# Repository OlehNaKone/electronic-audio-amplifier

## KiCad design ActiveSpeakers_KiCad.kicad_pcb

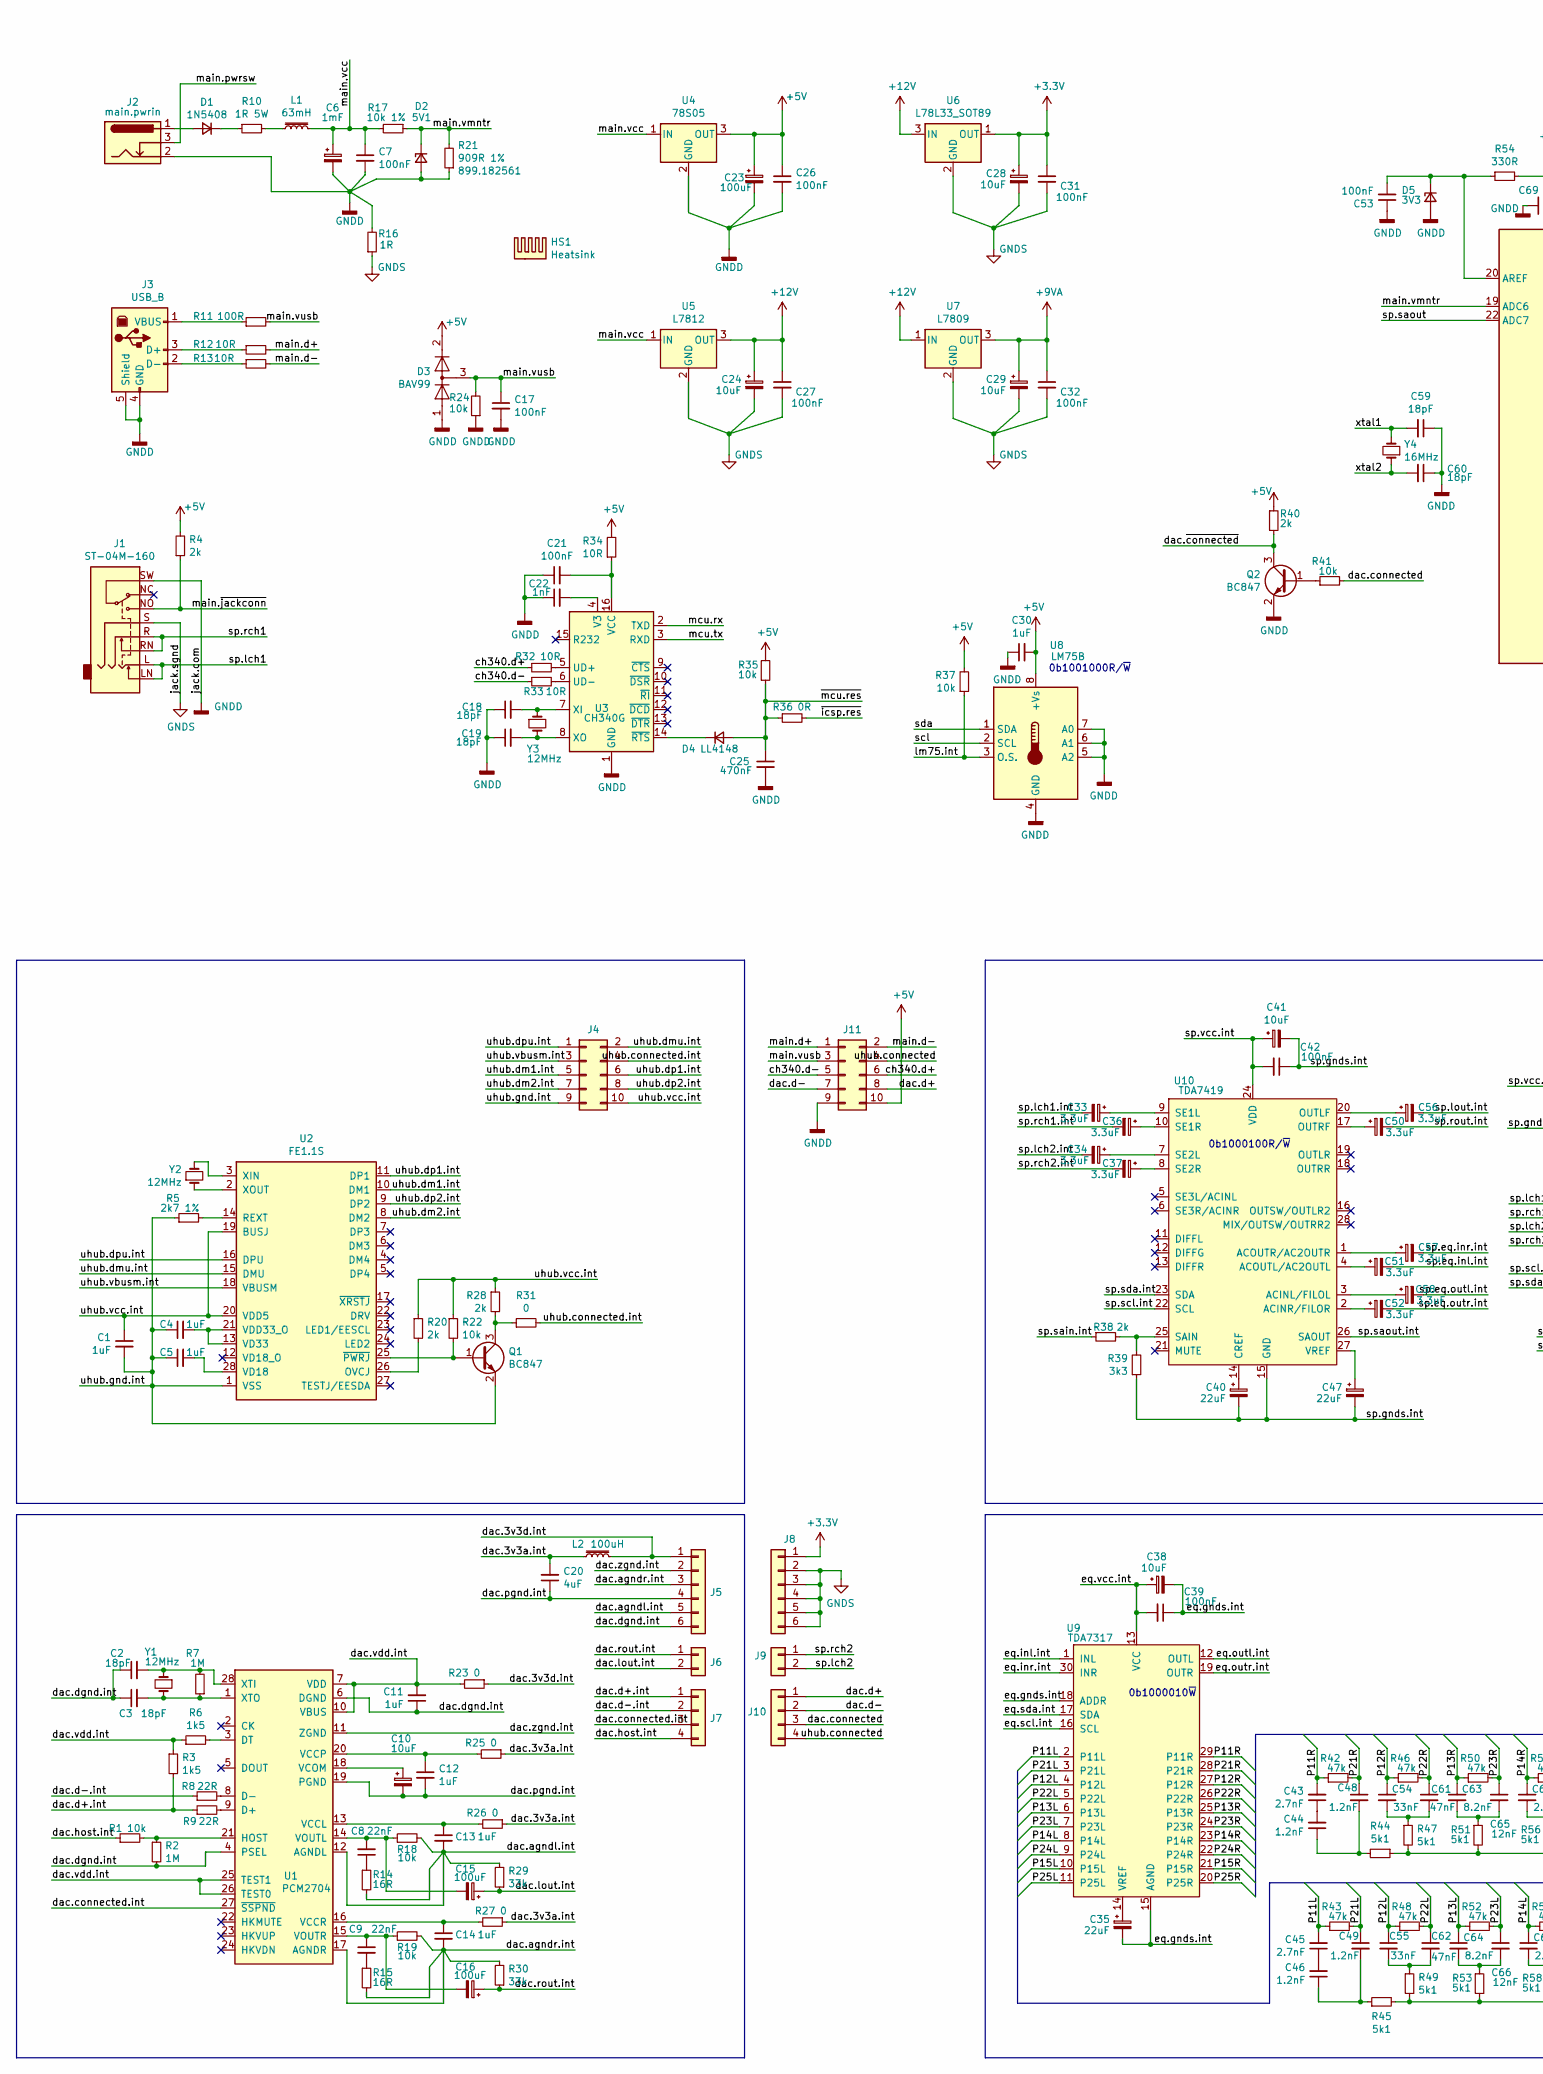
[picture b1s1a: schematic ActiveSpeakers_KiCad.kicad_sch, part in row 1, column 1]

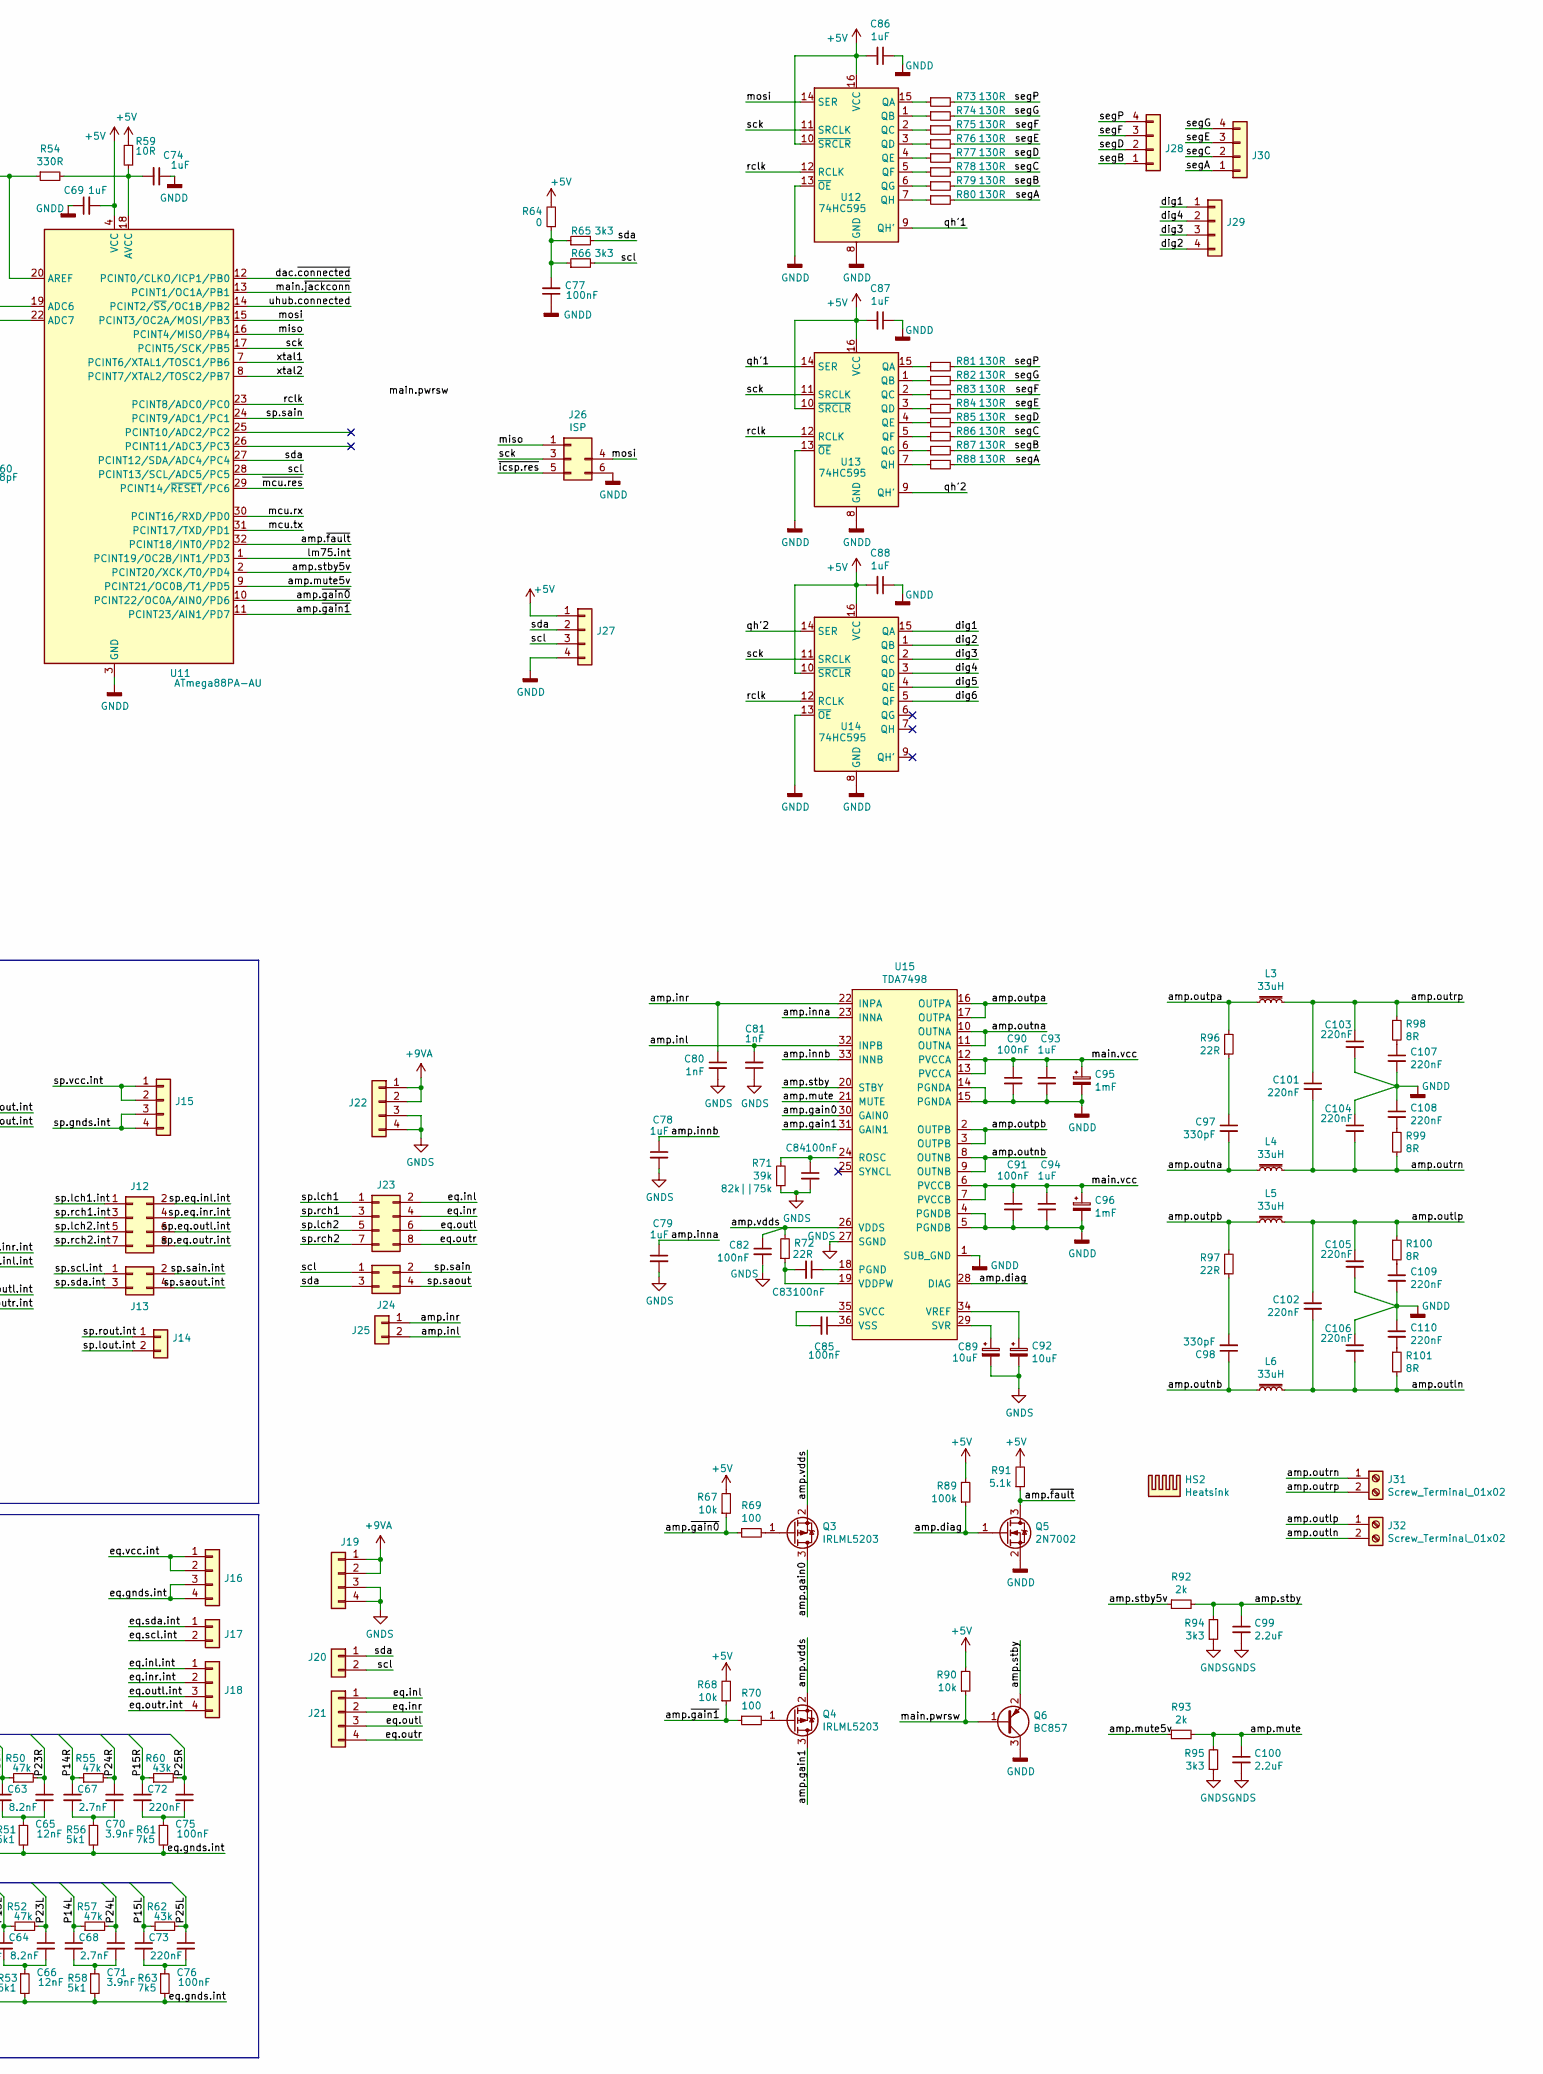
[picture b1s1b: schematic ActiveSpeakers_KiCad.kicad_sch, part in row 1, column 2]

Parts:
C1, C11, C12, C13, C14, C30, C69, C74, C86, C87, C88, C93, C94: 1uF; C_1206_3216Metric_Pad1.42x1.75mm_HandSolder
C2, C3, C18, C19, C59, C60: 18pF; C_0805_2012Metric_Pad1.15x1.40mm_HandSolder
C4, C5: 1uF; C_0805_2012Metric_Pad1.15x1.40mm_HandSolder
C6, C95, C96: 1mF; CP_Radial_D12.5mm_P5.00mm
C7, C39, C42, C75, C76: 100nF; C_Rect_L7.2mm_W2.5mm_P5.00mm_FKS2_FKP2_MKS2_MKP2
C8, C9: 22nF; C_Rect_Flat_L7.2mm_W2.5mm_P5.00mm_FKS2_FKP2_MKS2_MKP2
C10: 10uF; CP_Radial_D4.0mm_P2.00mm
C15, C16, C23: 100uF; CP_Radial_D6.3mm_P2.50mm
C17, C21, C26, C27, C31, C32, C53, C77, C83, C90, C91: 100nF; C_1206_3216Metric_Pad1.42x1.75mm_HandSolder
C20: 4uF; C_1206_3216Metric_Pad1.42x1.75mm_HandSolder
C22: 1nF; C_0805_2012Metric_Pad1.15x1.40mm_HandSolder
C24, C28, C29, C38, C41: 10uF; CP_Radial_D5.0mm_P2.54mm
C25: 470nF; C_1206_3216Metric_Pad1.42x1.75mm_HandSolder
C33, C34, C36, C37, C50, C51, C52, C56, C57, C58: 3.3uF; CP_Radial_D5.0mm_P2.54mm
C35, C40, C47: 22uF; CP_Radial_D5.0mm_P2.54mm
C43, C45: 2.7nF; C_Rect_L7.0mm_W3.5mm_P5.00mm
C44, C46, C48, C49: 1.2nF; C_Rect_L7.2mm_W2.5mm_P5.00mm_FKS2_FKP2_MKS2_MKP2
C54, C55: 33nF; C_Rect_L7.2mm_W2.5mm_P5.00mm_FKS2_FKP2_MKS2_MKP2
C61, C62: 47nF; C_Rect_L7.2mm_W2.5mm_P5.00mm_FKS2_FKP2_MKS2_MKP2
C63, C64: 8.2nF; C_Rect_L7.0mm_W3.5mm_P5.00mm
C65, C66: 12nF; C_Rect_L7.0mm_W3.5mm_P5.00mm
C67, C68: 2.7nF; C_Rect_L7.2mm_W2.5mm_P5.00mm_FKS2_FKP2_MKS2_MKP2
C70, C71: 3.9nF; C_Rect_L7.0mm_W3.5mm_P5.00mm
C72, C73, C103, C104, C105, C106, C107, C108, C109, C110: 220nF; C_Rect_L7.2mm_W2.5mm_P5.00mm_FKS2_FKP2_MKS2_MKP2
C78: 1uF; CP_Radial_Flat_Mirrored_D4.0mm_P2.00mm
C79: 1uF; CP_Radial_Flat_D4.0mm_P2.00mm
C80, C81: 1nF; C_Rect_Flat_L7.2mm_W2.5mm_P5.00mm_FKS2_FKP2_MKS2_MKP2
C82, C85: 100nF; C_0603_1608Metric_Pad1.05x0.95mm_HandSolder
C84: 100nF; C_0805_2012Metric_Pad1.15x1.40mm_HandSolder
C89, C92: 10uF; CP_Radial_Flat_Mirrored_D4.0mm_P2.00mm
C97, C98: 330pF; C_Rect_Flat_L7.2mm_W2.5mm_P5.00mm_FKS2_FKP2_MKS2_MKP2
C99, C100: 2.2uF; C_0805_2012Metric_Pad1.15x1.40mm_HandSolder
C101, C102: 220nF; C_Rect_L7.0mm_W3.5mm_P5.00mm
D1: 1N5408; D_DO-201AD_P12.70mm_Horizontal
D2: 5V1; D_MiniMELF
D3: BAV99; SOT-23
D4: LL4148; D_MiniMELF
D5: 3V3; D_MiniMELF
HS1: Heatsink; Heatsink_Fischer_SK104-STC-STIC_35x13mm_2xDrill2.5mm
HS2: Heatsink; Heatsink_50.2x72.1mm_4xFixation3mm
J1: ST-04M-160; Jack_3.5mm_CUI_SJ-3568N_Horizontal
J2: main.pwrin; BarrelJack_Horizontal
J3: USB_B; USB_B_OST_USB-B1HSxx_Horizontal
J4: Conn_02x05; PinHeader_2x05_P2.54mm_Horizontal
J5: Conn_01x06; PinHeader_1x06_P2.54mm_Horizontal
J6, J14, J17: Conn_01x04; PinHeader_1x02_P2.54mm_Horizontal
J7, J15, J16, J18: Conn_01x04; PinHeader_1x04_P2.54mm_Horizontal
J8: Conn_01x06; PinSocket_1x06_P2.54mm_Vertical
J9, J20, J25: Conn_01x04; PinSocket_1x02_P2.54mm_Vertical
J10, J19, J21, J22: Conn_01x04; PinSocket_1x04_P2.54mm_Vertical
J11: Conn_02x05; PinSocket_2x05_P2.54mm_Vertical
J12: Conn_02x04; PinHeader_2x04_P2.54mm_Horizontal
J13: Conn_01x04; PinHeader_2x02_P2.54mm_Horizontal
J23: Conn_01x04; PinSocket_2x04_P2.54mm_Vertical
J24: Conn_01x04; PinSocket_2x02_P2.54mm_Vertical
J26: ISP; AVR_ICSP_Without_VCC_P2.54mm
J27, J28, J29, J30: Conn_01x04; SolderWirePad_1x04_P3.175mm_Drill0.8mm
J31, J32: Screw_Terminal_01x02; TerminalBlock_bornier-2_P5.08mm
L1: 63mH; L_Toroid_Vertical_L17.8mm_W8.1mm_P7.62mm_Bourns_5700
L2: 100uH; L_1210_3225Metric_Pad1.42x2.65mm_HandSolder
L3, L4, L5, L6: 33uH; L_12x12mm_H8mm
Q1, Q2: BC847; SOT-23
Q3, Q4: IRLML5203; SOT-23
Q5: 2N7002; SOT-23
Q6: BC857; SOT-23
R1, R18, R19, R22, R37, R41, R67, R68, R90: 10k; R_0805_2012Metric_Pad1.15x1.40mm_HandSolder
R2, R7: 1M; R_1206_3216Metric_Pad1.42x1.75mm_HandSolder
R3, R6: 1k5; R_0603_1608Metric_Pad1.05x0.95mm_HandSolder
R4, R20, R28, R92, R93: 2k; R_0805_2012Metric_Pad1.15x1.40mm_HandSolder
R5: 2k7 1%; R_0805_2012Metric_Pad1.15x1.40mm_HandSolder
R8, R9: 22R; R_1206_3216Metric_Pad1.42x1.75mm_HandSolder
R10: 1R 5W; R_Axial_Power_L25.0mm_W9.0mm_P7.62mm_Vertical
R11: 100R; R_1206_3216Metric_Pad1.42x1.75mm_HandSolder
R12, R13, R32, R33, R34, R59: 10R; R_1206_3216Metric_Pad1.42x1.75mm_HandSolder
R14, R15: 16R; R_1206_3216Metric_Pad1.42x1.75mm_HandSolder
R16: 1R; R_2512_6332Metric_Pad1.52x3.35mm_HandSolder
R17: 10k 1%; R_0805_2012Metric_Pad1.15x1.40mm_HandSolder
R21: 909R 1%; R_0603_1608Metric_Pad1.05x0.95mm_HandSolder
R23, R25, R26, R27, R31, R64: 0; R_1206_3216Metric_Pad1.42x1.75mm_HandSolder
R24, R35: 10k; R_1206_3216Metric_Pad1.42x1.75mm_HandSolder
R29, R30: 33k; R_0805_2012Metric_Pad1.15x1.40mm_HandSolder
R36: 0R; R_1206_3216Metric_Pad1.42x1.75mm_HandSolder
R38, R40: 2k; R_1206_3216Metric_Pad1.42x1.75mm_HandSolder
R39: 3k3; R_1206_3216Metric_Pad1.42x1.75mm_HandSolder
R42, R43, R46, R48, R50, R52, R55, R57: 47k; R_0805_2012Metric_Pad1.15x1.40mm_HandSolder
R44, R45, R47, R49, R51, R53, R56, R58: 5k1; R_0805_2012Metric_Pad1.15x1.40mm_HandSolder
R54: 330R; R_1206_3216Metric_Pad1.42x1.75mm_HandSolder
R60, R62: 43k; R_0805_2012Metric_Pad1.15x1.40mm_HandSolder
R61, R63: 7k5; R_0805_2012Metric_Pad1.15x1.40mm_HandSolder
R65, R66, R94, R95: 3k3; R_0805_2012Metric_Pad1.15x1.40mm_HandSolder
R69, R70: 100; R_0805_2012Metric_Pad1.15x1.40mm_HandSolder
R71: 39k; R_0805_2012Metric_Pad1.15x1.40mm_HandSolder
R72: 22R; R_0805_2012Metric_Pad1.15x1.40mm_HandSolder
R73, R74, R75, R76, R77, R78, R79, R80, R81, R82, R83, R84, R85, R86, R87, R88: 130R; R_0805_2012Metric_Pad1.15x1.40mm_HandSolder
R89: 100k; R_0805_2012Metric_Pad1.15x1.40mm_HandSolder
R91: 5.1k; R_0805_2012Metric_Pad1.15x1.40mm_HandSolder
R96, R97: 22R; R_Axial_DIN0207_L6.3mm_D2.5mm_P10.16mm_Horizontal
R98, R99, R100, R101: 8R; R_2512_6332Metric_Pad1.52x3.35mm_HandSolder
U1: PCM2704; SSOP-28_5.3x10.2mm_P0.65mm
U2: FE1.1S; SSOP-28_3.9x9.9mm_P0.635mm
U3: CH340G; SOIC-16_3.9x9.9mm_P1.27mm
U4: 78S05; TO-220-3_Vertical
U5: L7812; TO-252-2
U6: L78L33_SOT89; SOT-89-3
U7: L7809; TO-252-2
U8: LM75B; SOIC-8_3.9x4.9mm_P1.27mm
U9: TDA7317; SDIP-30_W10.16mm
U10: TDA7419; SOIC-28W_7.5x17.9mm_P1.27mm
U11: ATmega88PA-AU; TQFP-32_7x7mm_P0.8mm
U12, U13, U14: 74HC595; SOIC-16_3.9x9.9mm_P1.27mm
U15: TDA7498; ST_PowerSSO-36_EPU_SlugUp
Y1: 12MHz; Crystal_SMD_HC49-SD
Y2: 12MHz; Crystal_DS26_D2.0mm_L6.0mm_Horizontal
Y3: 12MHz; Crystal_DS26_D2.0mm_L6.0mm_Horizontal_1EP_style2
Y4: 16MHz; Crystal_SMD_HC49-SD

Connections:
+3V3: C28.1, C31.1, J8.1, U6.1 (OUT)
+5V: C23.1, C26.1, C30.2, C69.2, C86.2, C87.2, C88.2, D3.2 (A), J11.10, J27.1, R4.2, R34.2, R35.2, R37.2, R40.1, R59.1, R64.2, R67.2, R68.2, R89.2, R90.2, R91.2, U4.3 (OUT), U8.8 (+Vs), U11.4 (VCC), U11.6 (VCC), U12.10 (~SRCLR), U12.16 (VCC), U13.10 (~SRCLR), U13.16 (VCC), U14.10 (~SRCLR), U14.16 (VCC)
+9VA: C29.1, C32.1, J19.1, J19.2, J22.1, J22.2, U7.3 (OUT)
+12V: C24.1, C27.1, U5.3 (OUT), U6.3 (IN), U7.1 (IN)
/P11L: C45.2, R43.1, U9.2 (P11L)
/P11R: C43.2, R42.1, U9.29 (P11R)
/P12L: C55.1, R48.1, U9.4 (P12L)
/P12R: C54.1, R46.1, U9.27 (P12R)
/P13L: C64.1, R52.1, U9.6 (P13L)
/P13R: C63.1, R50.1, U9.25 (P13R)
/P14L: C68.1, R57.1, U9.8 (P14L)
/P14R: C67.1, R55.1, U9.23 (P14R)
/P15L: C73.1, R62.1, U9.10 (P15L)
/P15R: C72.1, R60.1, U9.21 (P15R)
/P21L: C49.1, R43.2, U9.3 (P21L)
/P21R: C48.1, R42.2, U9.28 (P21R)
/P22L: C62.1, R48.2, U9.5 (P22L)
/P22R: C61.1, R46.2, U9.26 (P22R)
/P23L: C66.1, R52.2, U9.7 (P23L)
/P23R: C65.1, R50.2, U9.24 (P23R)
/P24L: C71.1, R57.2, U9.9 (P24L)
/P24R: C70.1, R55.2, U9.22 (P24R)
/P25L: C76.1, R62.2, U9.11 (P25L)
/P25R: C75.1, R60.2, U9.20 (P25R)
/amp.diag: Q5.1 (G), R89.1, U15.28 (DIAG)
/amp.gain0: Q3.3 (D), U15.30 (GAIN0)
/amp.gain1: Q4.3 (D), U15.31 (GAIN1)
/amp.inl: C81.2, J25.2, U15.32 (INPB)
/amp.inna: C79.1, U15.23 (INNA)
/amp.innb: C78.1, U15.33 (INNB)
/amp.inr: C80.1, J25.1, U15.22 (INPA)
/amp.mute: C100.1, R93.2, R95.2, U15.21 (MUTE)
/amp.mute5v: R93.1, U11.9 (PCINT21/OC0B/T1/PD5)
/amp.outln: C102.2, C106.2, J32.2, L6.2, R101.2
/amp.outlp: C102.1, C105.1, J32.1, L5.2, R100.1
/amp.outna: C97.2, L4.1, U15.10 (OUTNA), U15.11 (OUTNA)
/amp.outnb: C98.1, L6.1, U15.8 (OUTNB), U15.9 (OUTNB)
/amp.outpa: L3.1, R96.2, U15.16 (OUTPA), U15.17 (OUTPA)
/amp.outpb: L5.1, R97.2, U15.2 (OUTPB), U15.3 (OUTPB)
/amp.outrn: C101.2, C104.2, J31.1, L4.2, R99.2
/amp.outrp: C101.1, C103.1, J31.2, L3.2, R98.1
/amp.stby: C99.1, Q6.2 (E), R92.2, R94.2, U15.20 (STBY)
/amp.stby5v: R92.1, U11.2 (PCINT20/XCK/T0/PD4)
/amp.vdds: C82.1, Q3.2 (S), Q4.2 (S), R72.2, U15.26 (VDDS)
/amp.~fault: Q5.3 (D), R91.1, U11.32 (PCINT18/INT0/PD2)
/amp.~gain0: R67.1, R69.1, U11.10 (PCINT22/OC0A/AIN0/PD6)
/amp.~gain1: R68.1, R70.1, U11.11 (PCINT23/AIN1/PD7)
/ch340.d+: J11.6, R32.1
/ch340.d-: J11.5, R33.1
/dac.3v3a.int: C20.2, L2.1, R25.1, R26.1, R27.1
/dac.3v3d.int: J5.1, L2.2, R23.1
/dac.agndl.int: C13.2, J5.5, R14.2, R18.2, R29.2, U1.12 (AGNDL)
/dac.agndr.int: C14.2, J5.3, R15.2, R19.2, R30.2, U1.17 (AGNDR)
/dac.connected: J10.3, R41.2
/dac.connected.int: J7.3, U1.27 (~SSPND)
/dac.d+: J10.1, J11.8
/dac.d+.int: J7.1, R3.2, R9.1
/dac.d-: J10.2, J11.7
/dac.d-.int: J7.2, R8.1
/dac.dgnd.int: C2.1, C3.1, C11.1, J5.6, R2.2, U1.4 (PSEL), U1.6 (DGND)
/dac.host.int: J7.4, R1.1
/dac.lout.int: C15.1, J6.2, R29.1
/dac.pgnd.int: C10.2, C12.2, C20.1, J5.4, U1.19 (PGND)
/dac.rout.int: C16.1, J6.1, R30.1
/dac.vdd.int: C11.2, R3.1, R6.1, R23.2, U1.7 (VDD), U1.10 (VBUS), U1.25 (TEST1), U1.26 (TEST0)
/dac.zgnd.int: J5.2, U1.11 (ZGND)
/dac.~connected: Q2.3 (C), R40.2, U11.12 (PCINT0/CLKO/ICP1/PB0)
/dig1: J29.1, U14.15 (QA)
/dig2: J29.4, U14.1 (QB)
/dig3: J29.3, U14.2 (QC)
/dig4: J29.2, U14.3 (QD)
/eq.gnds.int: C35.2, C38.2, C39.1, J16.3, J16.4, R44.1, R45.2, R47.2, R49.2, R51.2, R53.2, R56.2, R58.2, R61.2, R63.2, U9.15 (AGND), U9.18 (ADDR)
/eq.inl: J21.1, J23.2
/eq.inl.int: J18.1, U9.1 (INL)
/eq.inr: J21.2, J23.4
/eq.inr.int: J18.2, U9.30 (INR)
/eq.outl: J21.3, J23.6
/eq.outl.int: J18.3, U9.12 (OUTL)
/eq.outr: J21.4, J23.8
/eq.outr.int: J18.4, U9.19 (OUTR)
/eq.scl.int: J17.2, U9.16 (SCL)
/eq.sda.int: J17.1, U9.17 (SDA)
/eq.vcc.int: C38.1, C39.2, J16.1, J16.2, U9.13 (VCC)
/lm75.int: R37.1, U8.3 (O.S.), U11.1 (PCINT19/OC2B/INT1/PD3)
/main.d+: J11.1, R12.2
/main.d-: J11.2, R13.2
/main.pwrsw: J2.3, Q6.1 (B), R90.1
/main.vcc: C6.1, C7.1, C90.1, C91.1, C93.1, C94.1, C95.1, C96.1, L1.2, R17.2, U4.1 (IN), U5.1 (IN), U15.6 (PVCCB), U15.7 (PVCCB), U15.12 (PVCCA), U15.13 (PVCCA)
/main.vmntr: D2.1 (K), R17.1, R21.2, U11.19 (ADC6)
/main.vusb: C17.1, D3.3 (K), J11.3, R11.2, R24.2
/main.~jackconn: J1.NO, R4.1, U11.13 (PCINT1/OC1A/PB1)
/mcu.rx: U3.2 (TXD), U11.30 (PCINT16/RXD/PD0)
/mcu.tx: U3.3 (RXD), U11.31 (PCINT17/TXD/PD1)
/miso: J26.1 (MISO), U11.16 (PCINT4/MISO/PB4)
/mosi: J26.4 (MOSI), U11.15 (PCINT3/OC2A/MOSI/PB3), U12.14 (SER)
/qh'1: U12.9 (QH'), U13.14 (SER)
/qh'2: U13.9 (QH'), U14.14 (SER)
/rclk: U11.23 (PCINT8/ADC0/PC0), U12.12 (RCLK), U13.12 (RCLK), U14.12 (RCLK)
/sck: J26.3 (SCK), U11.17 (PCINT5/SCK/PB5), U12.11 (SRCLK), U13.11 (SRCLK), U14.11 (SRCLK)
/scl: J20.2, J24.1, J27.3, R66.2, U8.2 (SCL), U11.28 (PCINT13/SCL/ADC5/PC5)
/sda: J20.1, J24.3, J27.2, R65.2, U8.1 (SDA), U11.27 (PCINT12/SDA/ADC4/PC4)
/segA: J30.1, R80.2, R88.2
/segB: J28.1, R79.2, R87.2
/segC: J30.2, R78.2, R86.2
/segD: J28.2, R77.2, R85.2
/segE: J30.3, R76.2, R84.2
/segF: J28.3, R75.2, R83.2
/segG: J30.4, R74.2, R82.2
/segP: J28.4, R73.2, R81.2
/sp.eq.inl.int: C51.2, J12.2
/sp.eq.inr.int: C57.2, J12.4
/sp.eq.outl.int: C58.2, J12.6
/sp.eq.outr.int: C52.2, J12.8
/sp.gnds.int: C40.2, C41.2, C42.1, C47.2, J15.3, J15.4, R39.1, U10.15 (GND)
/sp.lch1: J1.L, J1.LN, J23.1
/sp.lch1.int: C33.2, J12.1
/sp.lch2: J9.2, J23.5
/sp.lch2.int: C34.2, J12.5
/sp.lout.int: C56.2, J14.2
/sp.rch1: J1.R, J1.RN, J23.3
/sp.rch1.int: C36.2, J12.3
/sp.rch2: J9.1, J23.7
/sp.rch2.int: C37.2, J12.7
/sp.rout.int: C50.2, J14.1
/sp.sain: J24.2, U11.24 (PCINT9/ADC1/PC1)
/sp.sain.int: J13.2, R38.1
/sp.saout: J24.4, U11.22 (ADC7)
/sp.saout.int: J13.4, U10.26 (SAOUT)
/sp.scl.int: J13.1, U10.22 (SCL)
/sp.sda.int: J13.3, U10.23 (SDA)
/sp.vcc.int: C41.1, C42.2, J15.1, J15.2, U10.24 (VDD)
/uhub.connected: J10.4, J11.4, U11.14 (PCINT2/~SS/OC1B/PB2)
/uhub.connected.int: J4.4, R31.2
/uhub.dm1.int: J4.5, U2.10 (DM1)
/uhub.dm2.int: J4.7, U2.8 (DM2)
/uhub.dmu.int: J4.2, U2.15 (DMU)
/uhub.dp1.int: J4.6, U2.11 (DP1)
/uhub.dp2.int: J4.8, U2.9 (DP2)
/uhub.dpu.int: J4.1, U2.16 (DPU)
/uhub.gnd.int: C1.2, C4.1, C5.1, J4.9, Q1.2 (E), R5.1, U2.1 (VSS)
/uhub.vbusm.int: J4.3, U2.18 (VBUSM)
/uhub.vcc.int: C1.1, J4.10, R20.1, R22.1, R28.1, U2.19 (BUSJ), U2.20 (VDD5)
/xtal1: C59.2, U11.7 (PCINT6/XTAL1/TOSC1/PB6), Y4.2
/xtal2: C60.2, U11.8 (PCINT7/XTAL2/TOSC2/PB7), Y4.1
/~icsp.res: J26.5 (~RESET), R36.2
/~mcu.res: C25.1, D4.2 (A), R35.1, R36.1, U11.29 (PCINT14/~RESET/PC6)
GNDD: C6.2, C7.2, C17.2, C18.1, C19.1, C21.1, C22.1, C23.2, C25.2, C26.2, C30.1, C53.1, C59.1, C60.1, C69.1, C74.1, C77.1, C86.1, C87.1, C88.1, C90.2, C91.2, C93.2, C94.2, C95.2, C96.2, C103.2, C104.1, C105.2, C106.1, C107.2, C108.1, C109.2, C110.1, D2.2 (A), D3.1 (K), D5.2 (A), J1.SW, J2.2, J3.4 (GND), J3.5 (Shield), J11.9, J26.6 (GNDD), J27.4, Q2.2 (E), Q5.2 (S), Q6.3 (C), R16.2, R21.1, R24.1, U3.1 (GND), U4.2 (GND), U8.4 (GND), U8.5 (A2), U8.6 (A1), U8.7 (A0), U11.3 (GND), U11.5 (GND), U11.21 (GND), U12.8 (GND), U12.13 (~OE), U13.8 (GND), U13.13 (~OE), U14.8 (GND), U14.13 (~OE), U15.1 (SUB_GND), U15.4 (PGNDB), U15.5 (PGNDB), U15.14 (PGNDA), U15.15 (PGNDA)
GNDS: C24.2, C27.2, C28.2, C29.2, C31.2, C32.2, C78.2, C79.2, C80.2, C81.1, C82.2, C84.2, C89.2, C92.2, C99.2, C100.2, J1.S, J8.2, J8.3, J8.4, J8.5, J8.6, J19.3, J19.4, J22.3, J22.4, R16.1, R71.1, R94.1, R95.1, U5.2 (GND), U6.2 (GND), U7.2 (GND), U15.27 (SGND)
unnamed: C2.2, R7.2, U1.28 (XTI), Y1.1
unnamed: C3.2, R7.1, U1.1 (XTO), Y1.2
unnamed: C4.2, U2.13 (VD33), U2.21 (VDD33_O)
unnamed: C5.2, U2.28 (VD18)
unnamed: C8.1, R14.1
unnamed: C9.2, R15.1
unnamed: C10.1, U1.18 (VCOM)
unnamed: C12.1, R25.2, U1.20 (VCCP)
unnamed: C13.1, R26.2, U1.13 (VCCL)
unnamed: C14.1, R27.2, U1.16 (VCCR)
unnamed: C8.2, C15.2, R18.1, U1.14 (VOUTL)
unnamed: C9.1, C16.2, R19.1, U1.15 (VOUTR)
unnamed: C18.2, U3.7 (XI), Y3.1
unnamed: C19.2, U3.8 (XO), Y3.2
unnamed: C21.2, R34.1, U3.16 (VCC)
unnamed: C22.2, U3.4 (V3)
unnamed: C33.1, U10.9 (SE1L)
unnamed: C34.1, U10.7 (SE2L)
unnamed: C35.1, U9.14 (VREF)
unnamed: C36.1, U10.10 (SE1R)
unnamed: C37.1, U10.8 (SE2R)
unnamed: C40.1, U10.14 (CREF)
unnamed: C43.1, C44.2
unnamed: C44.1, C48.2, R44.2
unnamed: C45.1, C46.2
unnamed: C46.1, C49.2, R45.1
unnamed: C47.1, U10.27 (VREF)
unnamed: C50.1, U10.17 (OUTRF)
unnamed: C51.1, U10.4 (ACOUTL/AC2OUTL)
unnamed: C52.1, U10.2 (ACINR/FILOR)
unnamed: C53.2, D5.1 (K), R54.1, U11.20 (AREF)
unnamed: C54.2, C61.2, R47.1
unnamed: C55.2, C62.2, R49.1
unnamed: C56.1, U10.20 (OUTLF)
unnamed: C57.1, U10.1 (ACOUTR/AC2OUTR)
unnamed: C58.1, U10.3 (ACINL/FILOL)
unnamed: C63.2, C65.2, R51.1
unnamed: C64.2, C66.2, R53.1
unnamed: C67.2, C70.2, R56.1
unnamed: C68.2, C71.2, R58.1
unnamed: C72.2, C75.2, R61.1
unnamed: C73.2, C76.2, R63.1
unnamed: C74.2, R54.2, R59.2, U11.18 (AVCC)
unnamed: C77.2, R64.1, R65.1, R66.1
unnamed: C83.1, U15.18 (PGND)
unnamed: C83.2, R72.1, U15.19 (VDDPW)
unnamed: C84.1, R71.2, U15.24 (ROSC)
unnamed: C85.1, U15.36 (VSS)
unnamed: C85.2, U15.35 (SVCC)
unnamed: C89.1, U15.29 (SVR)
unnamed: C92.1, U15.34 (VREF)
unnamed: C97.1, R96.1
unnamed: C98.2, R97.1
unnamed: C107.1, R98.2
unnamed: C108.2, R99.1
unnamed: C109.1, R100.2
unnamed: C110.2, R101.1
unnamed: D1.1 (K), R10.1
unnamed: D1.2 (A), J2.1
unnamed: D4.1 (K), U3.14 (~RTS)
unnamed: J3.1 (VBUS), R11.1
unnamed: J3.2 (D-), R13.1
unnamed: J3.3 (D+), R12.1
unnamed: L1.1, R10.2
unnamed: Q1.1 (B), R22.2, U2.25 (~PWRJ)
unnamed: Q1.3 (C), R28.2, R31.1
unnamed: Q2.1 (B), R41.1
unnamed: Q3.1 (G), R69.2
unnamed: Q4.1 (G), R70.2
unnamed: R1.2, R2.1, U1.21 (HOST)
unnamed: R5.2, U2.14 (REXT)
unnamed: R6.2, U1.3 (DT)
unnamed: R8.2, U1.8 (D-)
unnamed: R9.2, U1.9 (D+)
unnamed: R20.2, U2.26 (OVCJ)
unnamed: R32.2, U3.5 (UD+)
unnamed: R33.2, U3.6 (UD-)
unnamed: R38.2, R39.2, U10.25 (SAIN)
unnamed: R73.1, U12.15 (QA)
unnamed: R74.1, U12.1 (QB)
unnamed: R75.1, U12.2 (QC)
unnamed: R76.1, U12.3 (QD)
unnamed: R77.1, U12.4 (QE)
unnamed: R78.1, U12.5 (QF)
unnamed: R79.1, U12.6 (QG)
unnamed: R80.1, U12.7 (QH)
unnamed: R81.1, U13.15 (QA)
unnamed: R82.1, U13.1 (QB)
unnamed: R83.1, U13.2 (QC)
unnamed: R84.1, U13.3 (QD)
unnamed: R85.1, U13.4 (QE)
unnamed: R86.1, U13.5 (QF)
unnamed: R87.1, U13.6 (QG)
unnamed: R88.1, U13.7 (QH)
unnamed: U2.2 (XOUT), Y2.1
unnamed: U2.3 (XIN), Y2.2

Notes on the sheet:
0b1000100R/~{W}
0b1000010~{W}
0b1001000R/~{W}

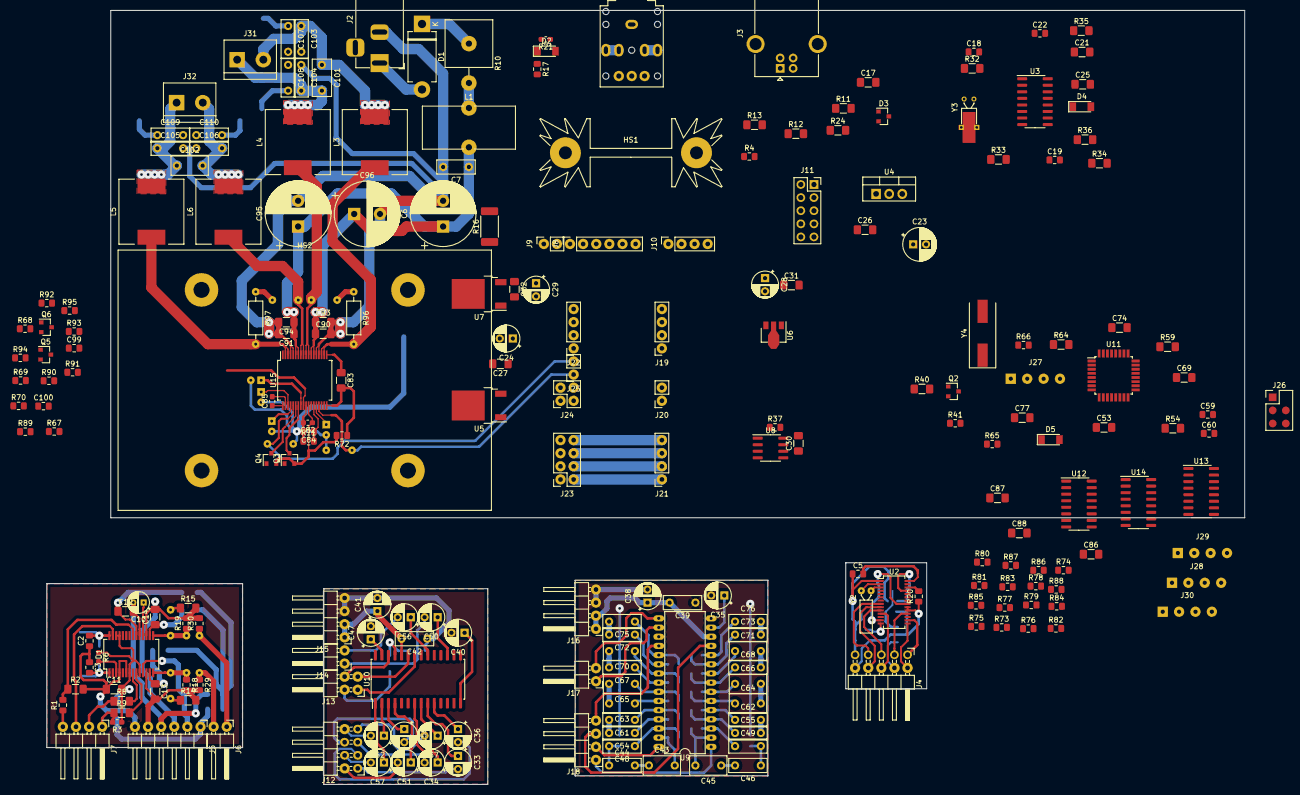
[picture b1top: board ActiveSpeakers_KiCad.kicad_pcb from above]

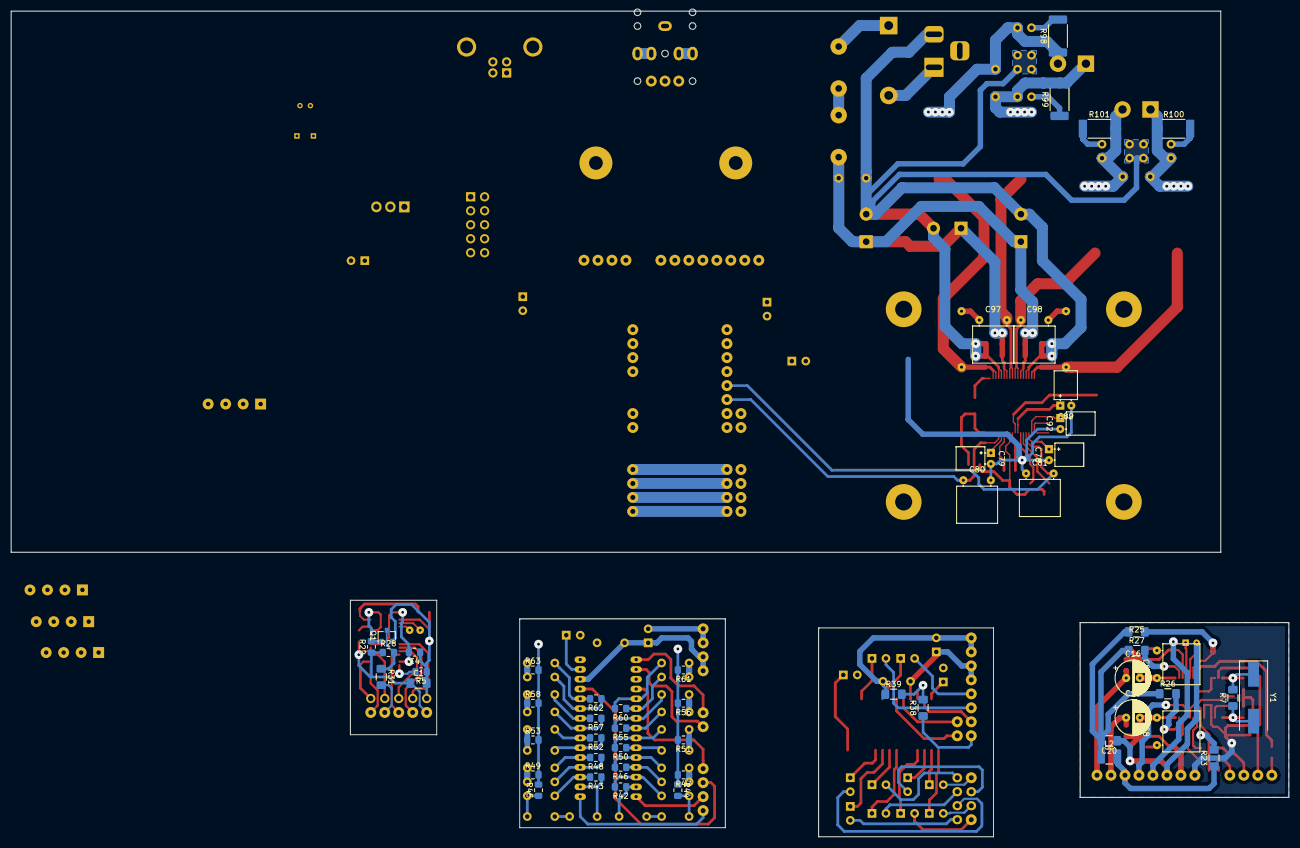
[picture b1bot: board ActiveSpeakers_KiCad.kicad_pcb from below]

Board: 2 copper layers, 232.1 x 150.0 mm, 281 parts (53 on the bottom side), 244 nets.

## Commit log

2022-04-06 init
